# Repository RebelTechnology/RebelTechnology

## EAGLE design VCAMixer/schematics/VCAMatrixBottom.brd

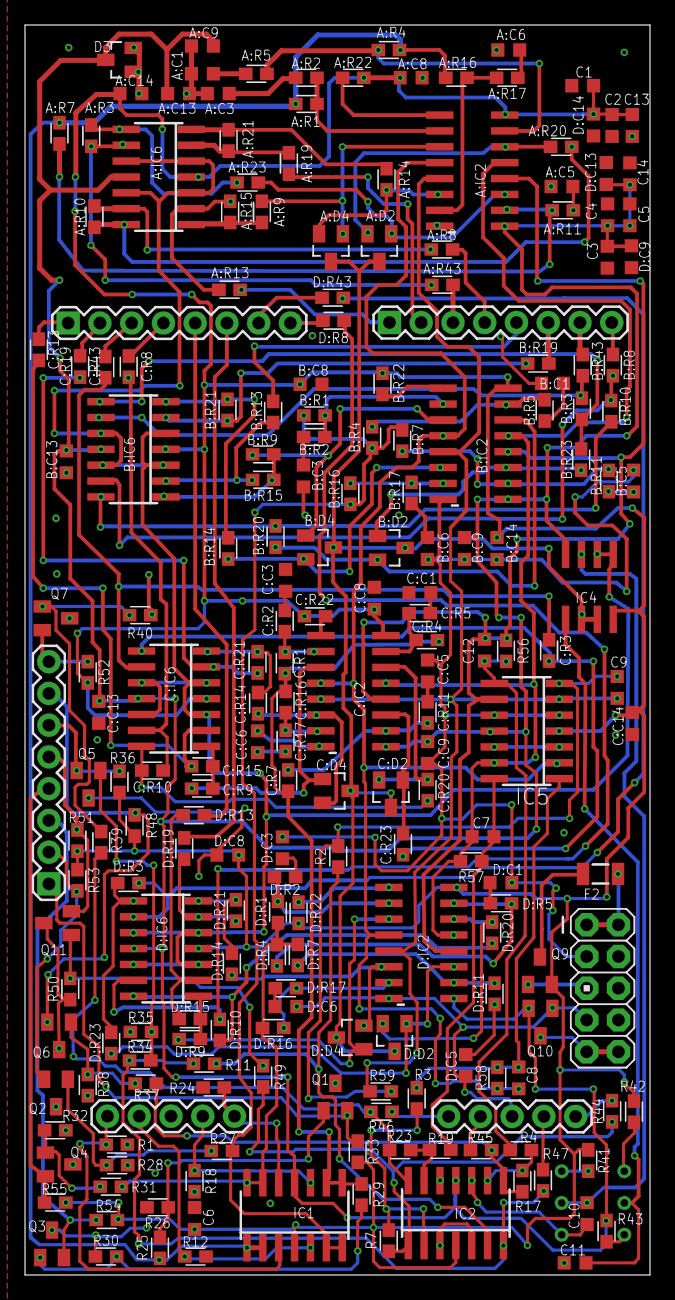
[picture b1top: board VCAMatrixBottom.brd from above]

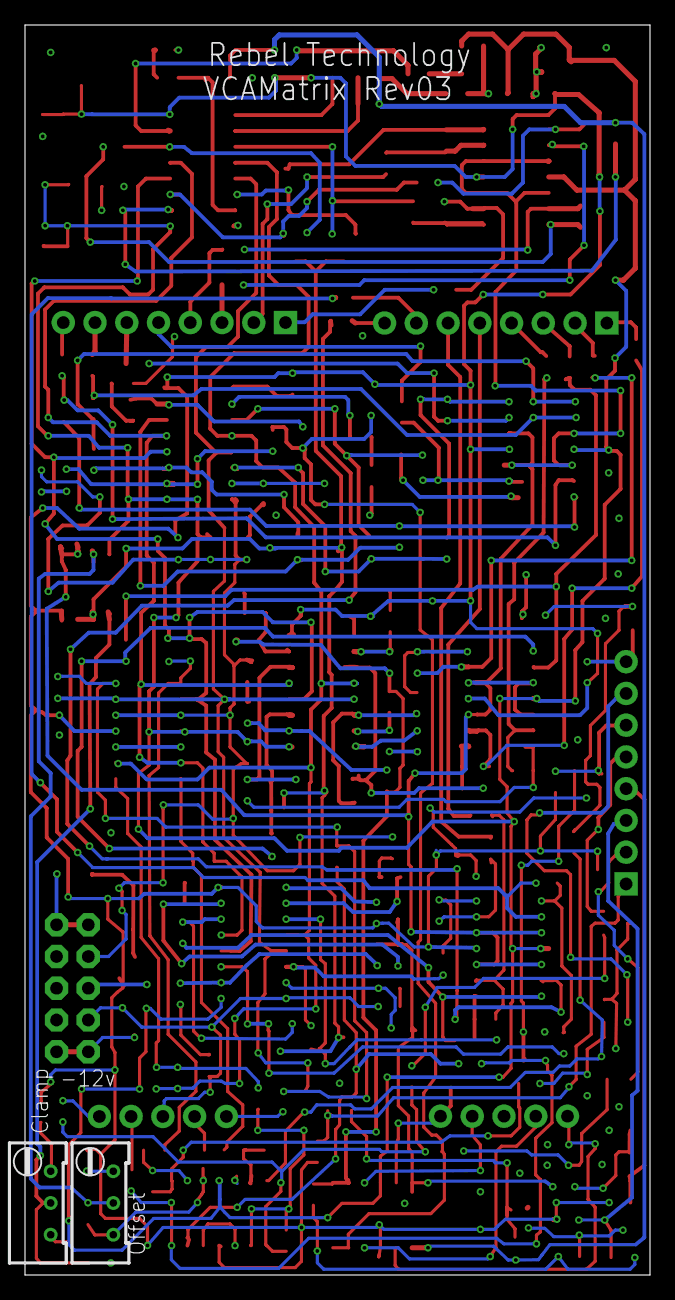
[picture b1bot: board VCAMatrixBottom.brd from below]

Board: 2 copper layers, 50.0 x 100.0 mm, 217 parts (2 on the bottom side), 157 nets.

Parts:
A:C1, A:C3, A:C5, A:C6: 560p; C0603K
A:C8, A:C9, A:C13, A:C14: 100n; C0603K
A:D2, A:D4: BAT54A; SOT23
A:IC2: SSM2164S; SOIC16N
A:IC6: QUAD_OPAMPD; SO14
A:R1, A:R4, A:R7, A:R16: 30k; 0603
A:R2, A:R5, A:R11, A:R17: 500; 0603
A:R3, A:R10, A:R15, A:R21: 68k; 0603
A:R8, A:R13, A:R19, A:R43: 100k; 0603
A:R9, A:R14, A:R20, A:R23: 560; 0603
A:R22: 5k6; 0603
B:C1, B:C3, B:C5, B:C6: 560p; C0603K
B:C8, B:C9, B:C13, B:C14: 100n; C0603K
B:D2, B:D4: BAT54A; SOT23
B:IC2: SSM2164S; SOIC16N
B:IC6: QUAD_OPAMPD; SO14
B:R1, B:R4, B:R7, B:R16: 30k; 0603
B:R2, B:R5, B:R11, B:R17: 500; 0603
B:R3, B:R10, B:R15, B:R21: 68k; 0603
B:R8, B:R13, B:R19, B:R43: 100k; 0603
B:R9, B:R14, B:R20, B:R23: 560; 0603
B:R22: 5k6; 0603
C1, C2, C3, C4, C5, C6, C13, C14: 100n; C0603K
C7, C8, C9, C12: 100p; C0603K
C10, C11: 4u7; C0603K
C:C1, C:C3, C:C5, C:C6: 560p; C0603K
C:C8, C:C9, C:C13, C:C14: 100n; C0603K
C:D2, C:D4: BAT54A; SOT23
C:IC2: SSM2164S; SOIC16N
C:IC6: QUAD_OPAMPD; SO14
C:R1, C:R4, C:R7, C:R16: 30k; 0603
C:R2, C:R5, C:R11, C:R17: 500; 0603
C:R3, C:R10, C:R15, C:R21: 68k; 0603
C:R8, C:R13, C:R19, C:R43: 100k; 0603
C:R9, C:R14, C:R20, C:R23: 560; 0603
C:R22: 5k6; 0603
CLAMP: RTRIM64W
D3: BAT54A; SOT23
D:C1, D:C3, D:C5, D:C6: 560p; C0603K
D:C8, D:C9, D:C13, D:C14: 100n; C0603K
D:D2, D:D4: BAT54A; SOT23
D:IC2: SSM2164S; SOIC16N
D:IC6: QUAD_OPAMPD; SO14
D:R1, D:R4, D:R7, D:R16: 30k; 0603
D:R2, D:R5, D:R11, D:R17: 500; 0603
D:R3, D:R10, D:R15, D:R21: 68k; 0603
D:R8, D:R13, D:R19, D:R43: 100k; 0603
D:R9, D:R14, D:R20, D:R23: 560; 0603
D:R22: 5k6; 0603
F2: PTCSMD; PTC-1206
IC1, IC2, IC5: QUAD_OPAMPD; SO14
IC4: TL072D; SO08
J3, J4: 1X05
JP1, JP3, JP5: 1X08
JP8: M05X2PTH; AVR_ICSP
OFFSET: RTRIM64W
Q1, Q2, Q3, Q4, Q5, Q6, Q7, Q11: BC856ALT1SMD; SOT23-BEC
Q9: BSS84; SOT23
Q10: BSS123; SOT23
R1, R2, R3, R4, R7, R11, R12, R17, R18, R19, R23, R24, R25, R27, R29, R31, R34, R37, R39, R49: 100k; 0603
R26, R28, R30, R32, R35, R38, R40, R50: 22k; 0603
R33, R36, R48, R51, R52, R53, R54, R55: 4k7; 0603
R41, R42, R43: 10k; 0603
R44, R45, R46, R47: 1k; 0603
R56, R57, R58, R59: 30k; 0603

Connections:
+12V: A:C8.1, A:C14.1, A:IC2.16, A:IC6.4, A:R22.2, B:C8.1, B:C14.1, B:IC2.16, B:IC6.4, B:R22.2, C1.1, C2.1, C6.1, C13.1, C:C8.1, C:C14.1, C:IC2.16, C:IC6.4, C:R22.2, D:C8.1, D:C14.1, D:IC2.16, D:IC6.4, D:R22.2, IC1.4, IC2.4, IC4.8, IC5.4, Q9.2, R33.2, R36.2, R41.2, R42.2, R48.2, R51.2, R52.2, R53.2, R54.2, R55.2
-12V: A:C9.2, A:C13.1, A:IC2.9, A:IC6.11, B:C9.2, B:C13.1, B:IC2.9, B:IC6.11, C3.1, C4.1, C5.1, C14.1, C:C9.2, C:C13.1, C:IC2.9, C:IC6.11, D3.3, D:C9.2, D:C13.1, D:IC2.9, D:IC6.11, IC1.11, IC2.11, IC4.4, IC5.11, Q10.2, R43.1
A:IC2_1: A:IC6.14, A:R10.1, A:R20.1
A:IC2_2: A:IC6.13, A:R8.1, A:R10.2
A:IC2_3: A:IC6.1, A:R9.1, A:R15.1
A:IC2_4: A:IC6.9, A:R3.2, A:R43.1
A:IC2_5: A:IC6.2, A:R13.1, A:R15.2
A:IC2_6: A:IC6.7, A:R14.1, A:R21.1
A:IC2_7: A:IC6.6, A:R19.1, A:R21.2
A:IC2_11: A:IC6.8, A:R3.1, A:R23.2
A:N$1: A:D4.1, A:IC2.3, A:R9.2
A:N$2: A:C1.1, A:R5.1
A:N$3: A:C3.1, A:R2.1
A:N$4: A:IC2.15, A:R4.2, A:R5.2
A:N$5: A:IC2.2, A:R1.2, A:R2.2
A:N$7: A:D4.2, A:IC2.6, A:R14.2
A:N$8: A:D2.1, A:IC2.11, A:R23.1
A:N$11: A:C6.1, A:R17.1
A:N$12: A:IC2.7, A:R16.2, A:R17.2
A:N$14: A:D2.2, A:IC2.14, A:R20.2
A:N$17: A:IC2.1, A:R22.1
A:N$19: A:C5.1, A:R11.1
A:N$23: A:IC2.10, A:R7.2, A:R11.2
B:IC2_1: B:IC6.14, B:R10.1, B:R20.1
B:IC2_2: B:IC6.13, B:R8.1, B:R10.2
B:IC2_3: B:IC6.1, B:R9.1, B:R15.1
B:IC2_4: B:IC6.9, B:R3.2, B:R43.1
B:IC2_5: B:IC6.2, B:R13.1, B:R15.2
B:IC2_6: B:IC6.7, B:R14.1, B:R21.1
B:IC2_7: B:IC6.6, B:R19.1, B:R21.2
B:IC2_11: B:IC6.8, B:R3.1, B:R23.2
B:N$1: B:D4.1, B:IC2.3, B:R9.2
B:N$2: B:C1.1, B:R5.1
B:N$3: B:C3.1, B:R2.1
B:N$4: B:IC2.15, B:R4.2, B:R5.2
B:N$5: B:IC2.2, B:R1.2, B:R2.2
B:N$7: B:D4.2, B:IC2.6, B:R14.2
B:N$8: B:D2.1, B:IC2.11, B:R23.1
B:N$11: B:C6.1, B:R17.1
B:N$12: B:IC2.7, B:R16.2, B:R17.2
B:N$14: B:D2.2, B:IC2.14, B:R20.2
B:N$17: B:IC2.1, B:R22.1
B:N$19: B:C5.1, B:R11.1
B:N$23: B:IC2.10, B:R7.2, B:R11.2
C:IC2_1: C:IC6.14, C:R10.1, C:R20.1
C:IC2_2: C:IC6.13, C:R8.1, C:R10.2
C:IC2_3: C:IC6.1, C:R9.1, C:R15.1
C:IC2_4: C:IC6.9, C:R3.2, C:R43.1
C:IC2_5: C:IC6.2, C:R13.1, C:R15.2
C:IC2_6: C:IC6.7, C:R14.1, C:R21.1
C:IC2_7: C:IC6.6, C:R19.1, C:R21.2
C:IC2_11: C:IC6.8, C:R3.1, C:R23.2
C:N$1: C:D4.1, C:IC2.3, C:R9.2
C:N$2: C:C1.1, C:R5.1
C:N$3: C:C3.1, C:R2.1
C:N$4: C:IC2.15, C:R4.2, C:R5.2
C:N$5: C:IC2.2, C:R1.2, C:R2.2
C:N$7: C:D4.2, C:IC2.6, C:R14.2
C:N$8: C:D2.1, C:IC2.11, C:R23.1
C:N$11: C:C6.1, C:R17.1
C:N$12: C:IC2.7, C:R16.2, C:R17.2
C:N$14: C:D2.2, C:IC2.14, C:R20.2
C:N$17: C:IC2.1, C:R22.1
C:N$19: C:C5.1, C:R11.1
C:N$23: C:IC2.10, C:R7.2, C:R11.2
CLAMP_REF: A:D2.3, A:D4.3, B:D2.3, B:D4.3, C:D2.3, C:D4.3, D:D2.3, D:D4.3, IC4.6, IC4.7
CV_AA: A:R13.2, JP1.1
CV_AB: A:R19.2, JP1.2
CV_AC: A:R43.2, JP1.3
CV_AD: A:R8.2, JP1.4
CV_BA: B:R13.2, JP1.5
CV_BB: B:R19.2, JP1.6
CV_BC: B:R43.2, JP1.7
CV_BD: B:R8.2, JP1.8
CV_CA: C:R13.2, JP3.1
CV_CB: C:R19.2, JP3.2
CV_CC: C:R43.2, JP3.3
CV_CD: C:R8.2, JP3.4
CV_DA: D:R13.2, JP3.5
CV_DB: D:R19.2, JP3.6
CV_DC: D:R43.2, JP3.7
CV_DD: D:R8.2, JP3.8
D:IC2_1: D:IC6.14, D:R10.1, D:R20.1
D:IC2_2: D:IC6.13, D:R8.1, D:R10.2
D:IC2_3: D:IC6.1, D:R9.1, D:R15.1
D:IC2_4: D:IC6.9, D:R3.2, D:R43.1
D:IC2_5: D:IC6.2, D:R13.1, D:R15.2
D:IC2_6: D:IC6.7, D:R14.1, D:R21.1
D:IC2_7: D:IC6.6, D:R19.1, D:R21.2
D:IC2_11: D:IC6.8, D:R3.1, D:R23.2
D:N$1: D:D4.1, D:IC2.3, D:R9.2
D:N$2: D:C1.1, D:R5.1
D:N$3: D:C3.1, D:R2.1
D:N$4: D:IC2.15, D:R4.2, D:R5.2
D:N$5: D:IC2.2, D:R1.2, D:R2.2
D:N$7: D:D4.2, D:IC2.6, D:R14.2
D:N$8: D:D2.1, D:IC2.11, D:R23.1
D:N$11: D:C6.1, D:R17.1
D:N$12: D:IC2.7, D:R16.2, D:R17.2
D:N$14: D:D2.2, D:IC2.14, D:R20.2
D:N$17: D:IC2.1, D:R22.1
D:N$19: D:C5.1, D:R11.1
D:N$23: D:IC2.10, D:R7.2, D:R11.2
GND: A:C1.2, A:C3.2, A:C5.2, A:C6.2, A:C8.2, A:C9.1, A:C13.2, A:C14.2, A:IC2.8, B:C1.2, B:C3.2, B:C5.2, B:C6.2, B:C8.2, B:C9.1, B:C13.2, B:C14.2, B:IC2.8, C1.2, C2.2, C3.2, C4.2, C5.2, C6.2, C10.2, C11.2, C13.2, C14.2, C:C1.2, C:C3.2, C:C5.2, C:C6.2, C:C8.2, C:C9.1, C:C13.2, C:C14.2, C:IC2.8, D3.1, D3.2, D:C1.2, D:C3.2, D:C5.2, D:C6.2, D:C8.2, D:C9.1, D:C13.2, D:C14.2, D:IC2.8, IC2.3, IC2.5, IC2.10, IC2.12, IC5.3, IC5.5, IC5.10, IC5.12, J3.3, J4.3, JP8.3, JP8.4, JP8.5, JP8.6, JP8.7, JP8.8, OFFSET.1, Q1.C, Q2.C, Q3.C, Q4.C, Q5.C, Q6.C, Q7.C, Q9.1, Q10.1, Q11.C, R1.1, R12.1, R18.1, R24.1, R26.1, R28.1, R30.1, R32.1, R35.1, R38.1, R40.1, R50.1
IN_A: IC1.3, J3.5, R1.2
IN_B: IC1.5, J3.4, R12.2
IN_C: IC1.10, J3.2, R18.2
IN_D: IC1.12, J3.1, R24.2
ITOV_A: C8.1, IC5.1, R3.1, R58.2
ITOV_B: C9.1, IC5.7, R2.1, R59.2
ITOV_C: C12.1, IC5.8, R4.1, R56.2
ITOV_D: C7.1, IC5.14, R19.1, R57.2
LED_1: JP5.1, Q1.E, R33.1
LED_2: JP5.2, Q2.E, R53.1
LED_3: JP5.3, Q3.E, R54.1
LED_4: JP5.4, Q4.E, R55.1
LED_5: JP5.5, Q11.E, R51.1
LED_6: JP5.6, Q5.E, R36.1
LED_7: JP5.7, Q6.E, R48.1
LED_8: JP5.8, Q7.E, R52.1
unnamed: B:R1.1, B:R4.1, B:R7.1, B:R16.1, IC1.6, IC1.7, R27.1
unnamed: Q1.B, R25.2, R26.2
unnamed: JP8.9, JP8.10, Q10.3
unnamed: Q2.B, R27.2, R28.2
unnamed: IC2.2, R3.2, R7.1
unnamed: A:IC2.4, B:IC2.4, C8.2, C:IC2.4, D:IC2.4, IC5.2, R58.1
unnamed: A:IC2.12, B:IC2.12, C12.2, C:IC2.12, D:IC2.12, IC5.9, R56.1
unnamed: A:IC2.5, B:IC2.5, C9.2, C:IC2.5, D:IC2.5, IC5.6, R59.1
unnamed: IC2.9, R4.2, R17.1
unnamed: Q11.B, R49.2, R50.2
unnamed: OFFSET.3, R41.1
unnamed: Q5.B, R34.2, R35.2
unnamed: Q6.B, R37.2, R38.2
unnamed: Q7.B, R39.2, R40.2
unnamed: F2.2, Q9.3
unnamed: A:IC2.13, B:IC2.13, C7.2, C:IC2.13, D:IC2.13, IC5.13, R57.1
unnamed: Q3.B, R29.2, R30.2
unnamed: D:R1.1, D:R4.1, D:R7.1, D:R16.1, IC1.13, IC1.14, R31.1
unnamed: C:R1.1, C:R4.1, C:R7.1, C:R16.1, IC1.8, IC1.9, R29.1
unnamed: Q4.B, R31.2, R32.2
unnamed: C10.1, IC4.3, OFFSET.2
unnamed: CLAMP.3, R42.1
unnamed: IC2.13, R19.2, R23.1
unnamed: IC2.6, R2.2, R11.1
unnamed: CLAMP.1, R43.2
unnamed: C11.1, CLAMP.2, IC4.5
unnamed: F2.1, JP8.1, JP8.2
unnamed: A:R1.1, A:R4.1, A:R7.1, A:R16.1, IC1.1, IC1.2, R25.1
OFFSET_REF: A:IC6.3, A:IC6.5, A:IC6.10, A:IC6.12, B:IC6.3, B:IC6.5, B:IC6.10, B:IC6.12, C:IC6.3, C:IC6.5, C:IC6.10, C:IC6.12, D:IC6.3, D:IC6.5, D:IC6.10, D:IC6.12, IC4.1, IC4.2
OUTPUT_A: J4.5, R44.1
OUTPUT_B: J4.4, R47.1
OUTPUT_C: J4.2, R45.1
OUTPUT_D: J4.1, R46.1
OUT_A: IC2.1, R7.2, R44.2, R49.1
OUT_B: IC2.7, R11.2, R34.1, R47.2
OUT_C: IC2.8, R17.2, R37.1, R45.2
OUT_D: IC2.14, R23.2, R39.1, R46.2

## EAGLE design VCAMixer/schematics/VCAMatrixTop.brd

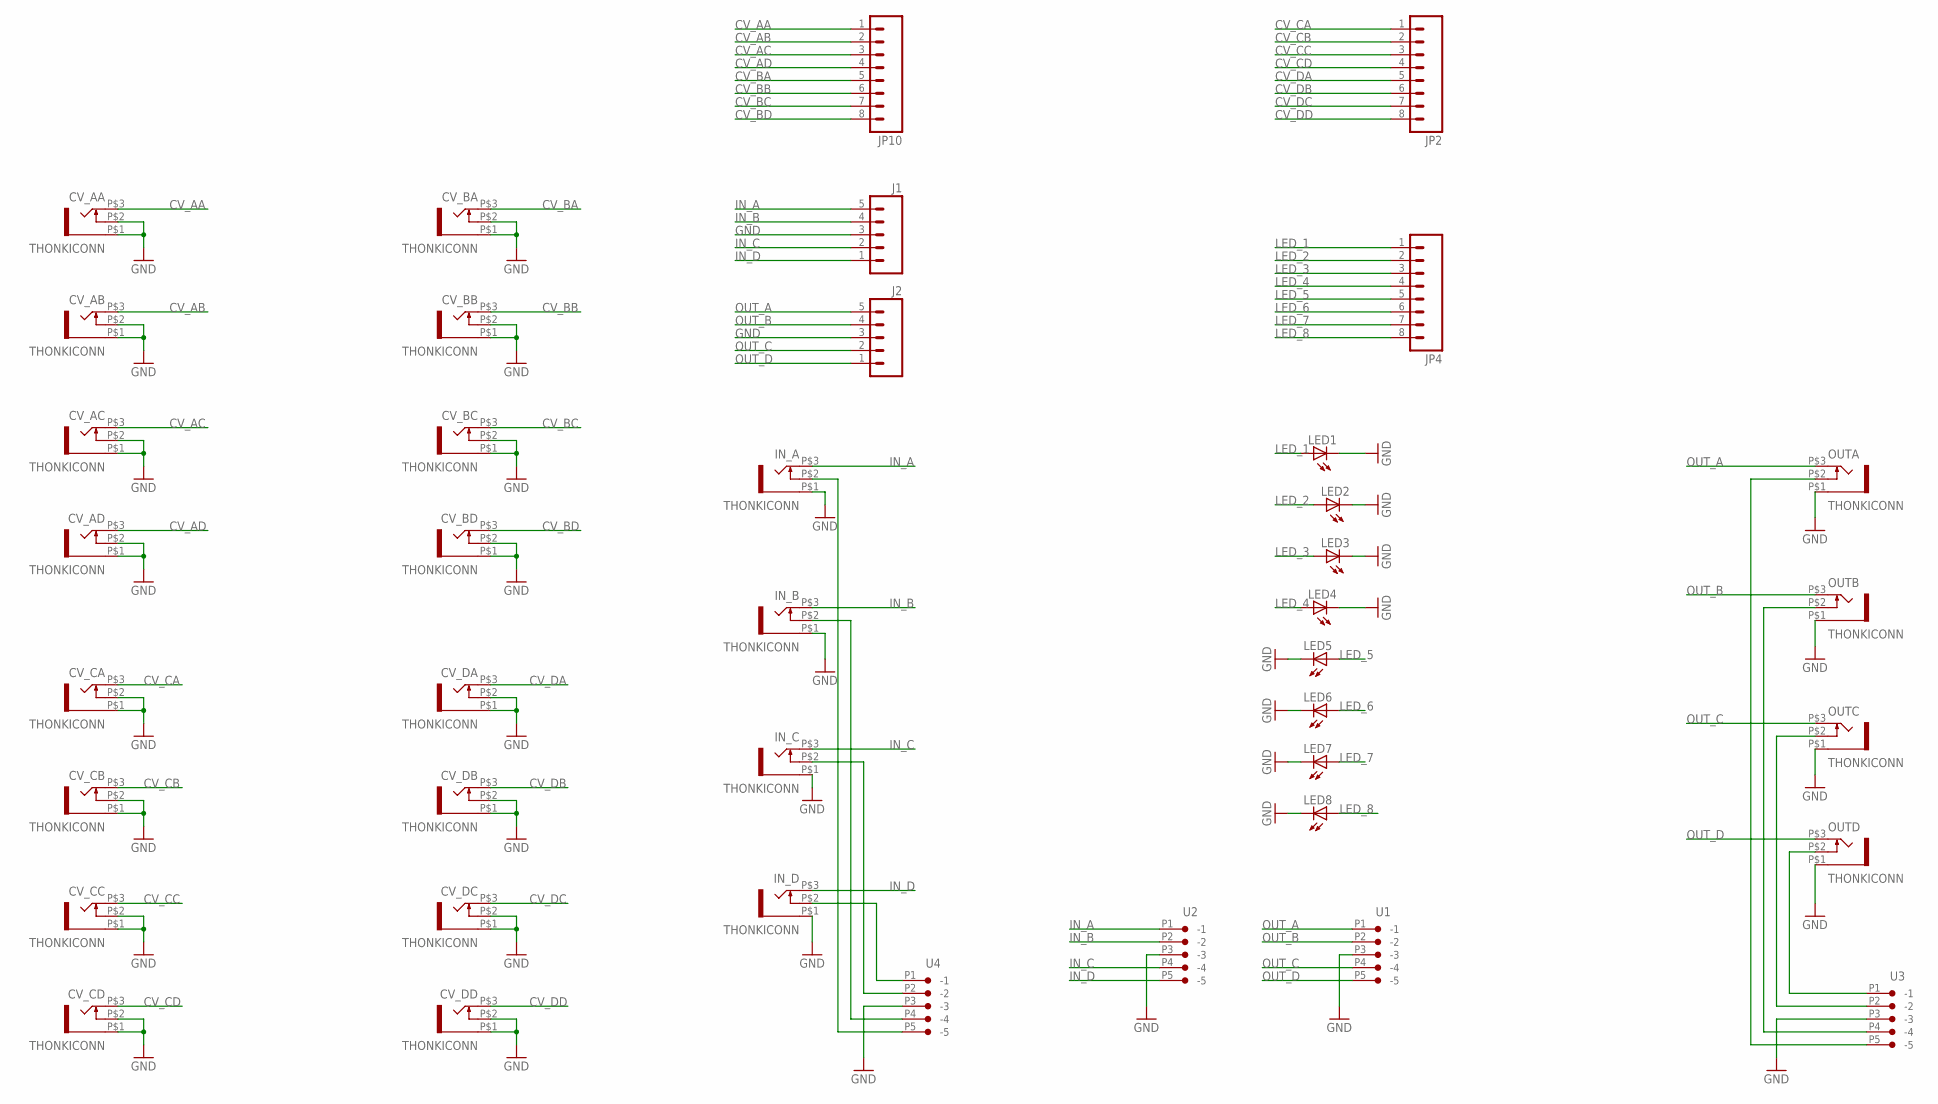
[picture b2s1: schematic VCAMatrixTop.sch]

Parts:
CV_AA: THONKICONN
CV_AB: THONKICONN
CV_AC: THONKICONN
CV_AD: THONKICONN
CV_BA: THONKICONN
CV_BB: THONKICONN
CV_BC: THONKICONN
CV_BD: THONKICONN
CV_CA: THONKICONN
CV_CB: THONKICONN
CV_CC: THONKICONN
CV_CD: THONKICONN
CV_DA: THONKICONN
CV_DB: THONKICONN
CV_DC: THONKICONN
CV_DD: THONKICONN
IN_A: THONKICONN
IN_B: THONKICONN
IN_C: THONKICONN
IN_D: THONKICONN
J1, J2: M05PTH; 1X05
JP2, JP4, JP10: M081X08; 1X08
LED1, LED2, LED3, LED4, LED5, LED6, LED7, LED8: LED3MM
OUTA: THONKICONN
OUTB: THONKICONN
OUTC: THONKICONN
OUTD: THONKICONN
U1, U2, U3, U4: CON-JST_PH_5W

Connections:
CV_AA: CV_AA.P$3 (3), JP10.1
CV_AB: CV_AB.P$3 (3), JP10.2
CV_AC: CV_AC.P$3 (3), JP10.3
CV_AD: CV_AD.P$3 (3), JP10.4
CV_BA: CV_BA.P$3 (3), JP10.5
CV_BB: CV_BB.P$3 (3), JP10.6
CV_BC: CV_BC.P$3 (3), JP10.7
CV_BD: CV_BD.P$3 (3), JP10.8
CV_CA: CV_CA.P$3 (3), JP2.1
CV_CB: CV_CB.P$3 (3), JP2.2
CV_CC: CV_CC.P$3 (3), JP2.3
CV_CD: CV_CD.P$3 (3), JP2.4
CV_DA: CV_DA.P$3 (3), JP2.5
CV_DB: CV_DB.P$3 (3), JP2.6
CV_DC: CV_DC.P$3 (3), JP2.7
CV_DD: CV_DD.P$3 (3), JP2.8
GND: CV_AA.P$1 (5), CV_AA.P$2 (4), CV_AB.P$1 (5), CV_AB.P$2 (4), CV_AC.P$1 (5), CV_AC.P$2 (4), CV_AD.P$1 (5), CV_AD.P$2 (4), CV_BA.P$1 (5), CV_BA.P$2 (4), CV_BB.P$1 (5), CV_BB.P$2 (4), CV_BC.P$1 (5), CV_BC.P$2 (4), CV_BD.P$1 (5), CV_BD.P$2 (4), CV_CA.P$1 (5), CV_CA.P$2 (4), CV_CB.P$1 (5), CV_CB.P$2 (4), CV_CC.P$1 (5), CV_CC.P$2 (4), CV_CD.P$1 (5), CV_CD.P$2 (4), CV_DA.P$1 (5), CV_DA.P$2 (4), CV_DB.P$1 (5), CV_DB.P$2 (4), CV_DC.P$1 (5), CV_DC.P$2 (4), CV_DD.P$1 (5), CV_DD.P$2 (4), IN_A.P$1 (5), IN_B.P$1 (5), IN_C.P$1 (5), IN_D.P$1 (5), J1.3, J2.3, LED1.K (C), LED2.K (C), LED3.K (C), LED4.K (C), LED5.K (C), LED6.K (C), LED7.K (C), LED8.K (C), OUTA.P$1 (5), OUTB.P$1 (5), OUTC.P$1 (5), OUTD.P$1 (5), U1.P3 (-3), U2.P3 (-3), U3.P3 (-3), U4.P3 (-3)
IN_A: IN_A.P$3 (3), J1.5, U2.P1 (-1)
IN_B: IN_B.P$3 (3), J1.4, U2.P2 (-2)
IN_C: IN_C.P$3 (3), J1.2, U2.P4 (-4)
IN_D: IN_D.P$3 (3), J1.1, U2.P5 (-5)
LED_1: JP4.1, LED1.A
LED_2: JP4.2, LED2.A
LED_3: JP4.3, LED3.A
LED_4: JP4.4, LED4.A
LED_5: JP4.5, LED5.A
LED_6: JP4.6, LED6.A
LED_7: JP4.7, LED7.A
LED_8: JP4.8, LED8.A
unnamed: OUTA.P$2 (4), U3.P5 (-5)
unnamed: IN_B.P$2 (4), U4.P4 (-4)
unnamed: IN_C.P$2 (4), U4.P2 (-2)
unnamed: IN_D.P$2 (4), U4.P1 (-1)
unnamed: OUTB.P$2 (4), U3.P4 (-4)
unnamed: OUTC.P$2 (4), U3.P2 (-2)
unnamed: OUTD.P$2 (4), U3.P1 (-1)
unnamed: IN_A.P$2 (4), U4.P5 (-5)
OUT_A: J2.5, OUTA.P$3 (3), U1.P1 (-1)
OUT_B: J2.4, OUTB.P$3 (3), U1.P2 (-2)
OUT_C: J2.2, OUTC.P$3 (3), U1.P4 (-4)
OUT_D: J2.1, OUTD.P$3 (3), U1.P5 (-5)

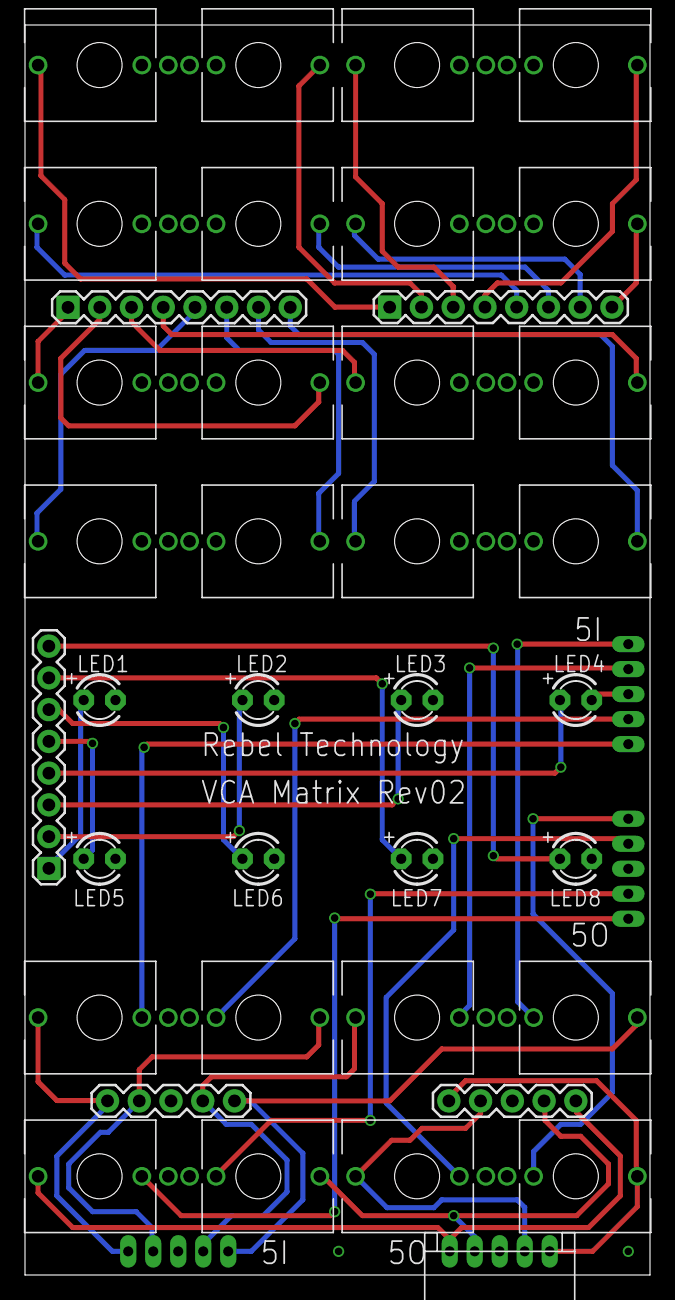
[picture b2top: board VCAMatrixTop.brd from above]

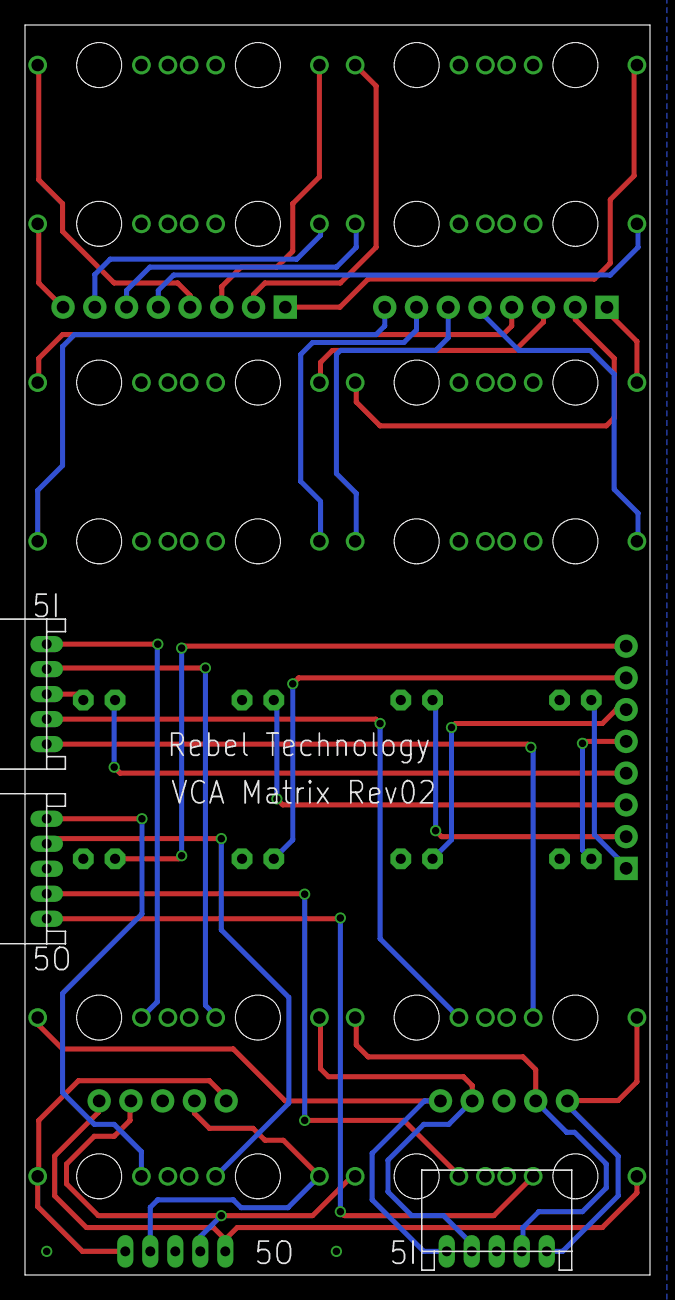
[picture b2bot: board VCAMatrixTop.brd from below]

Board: 2 copper layers, 50.0 x 100.0 mm, 41 parts (3 on the bottom side), 41 nets.

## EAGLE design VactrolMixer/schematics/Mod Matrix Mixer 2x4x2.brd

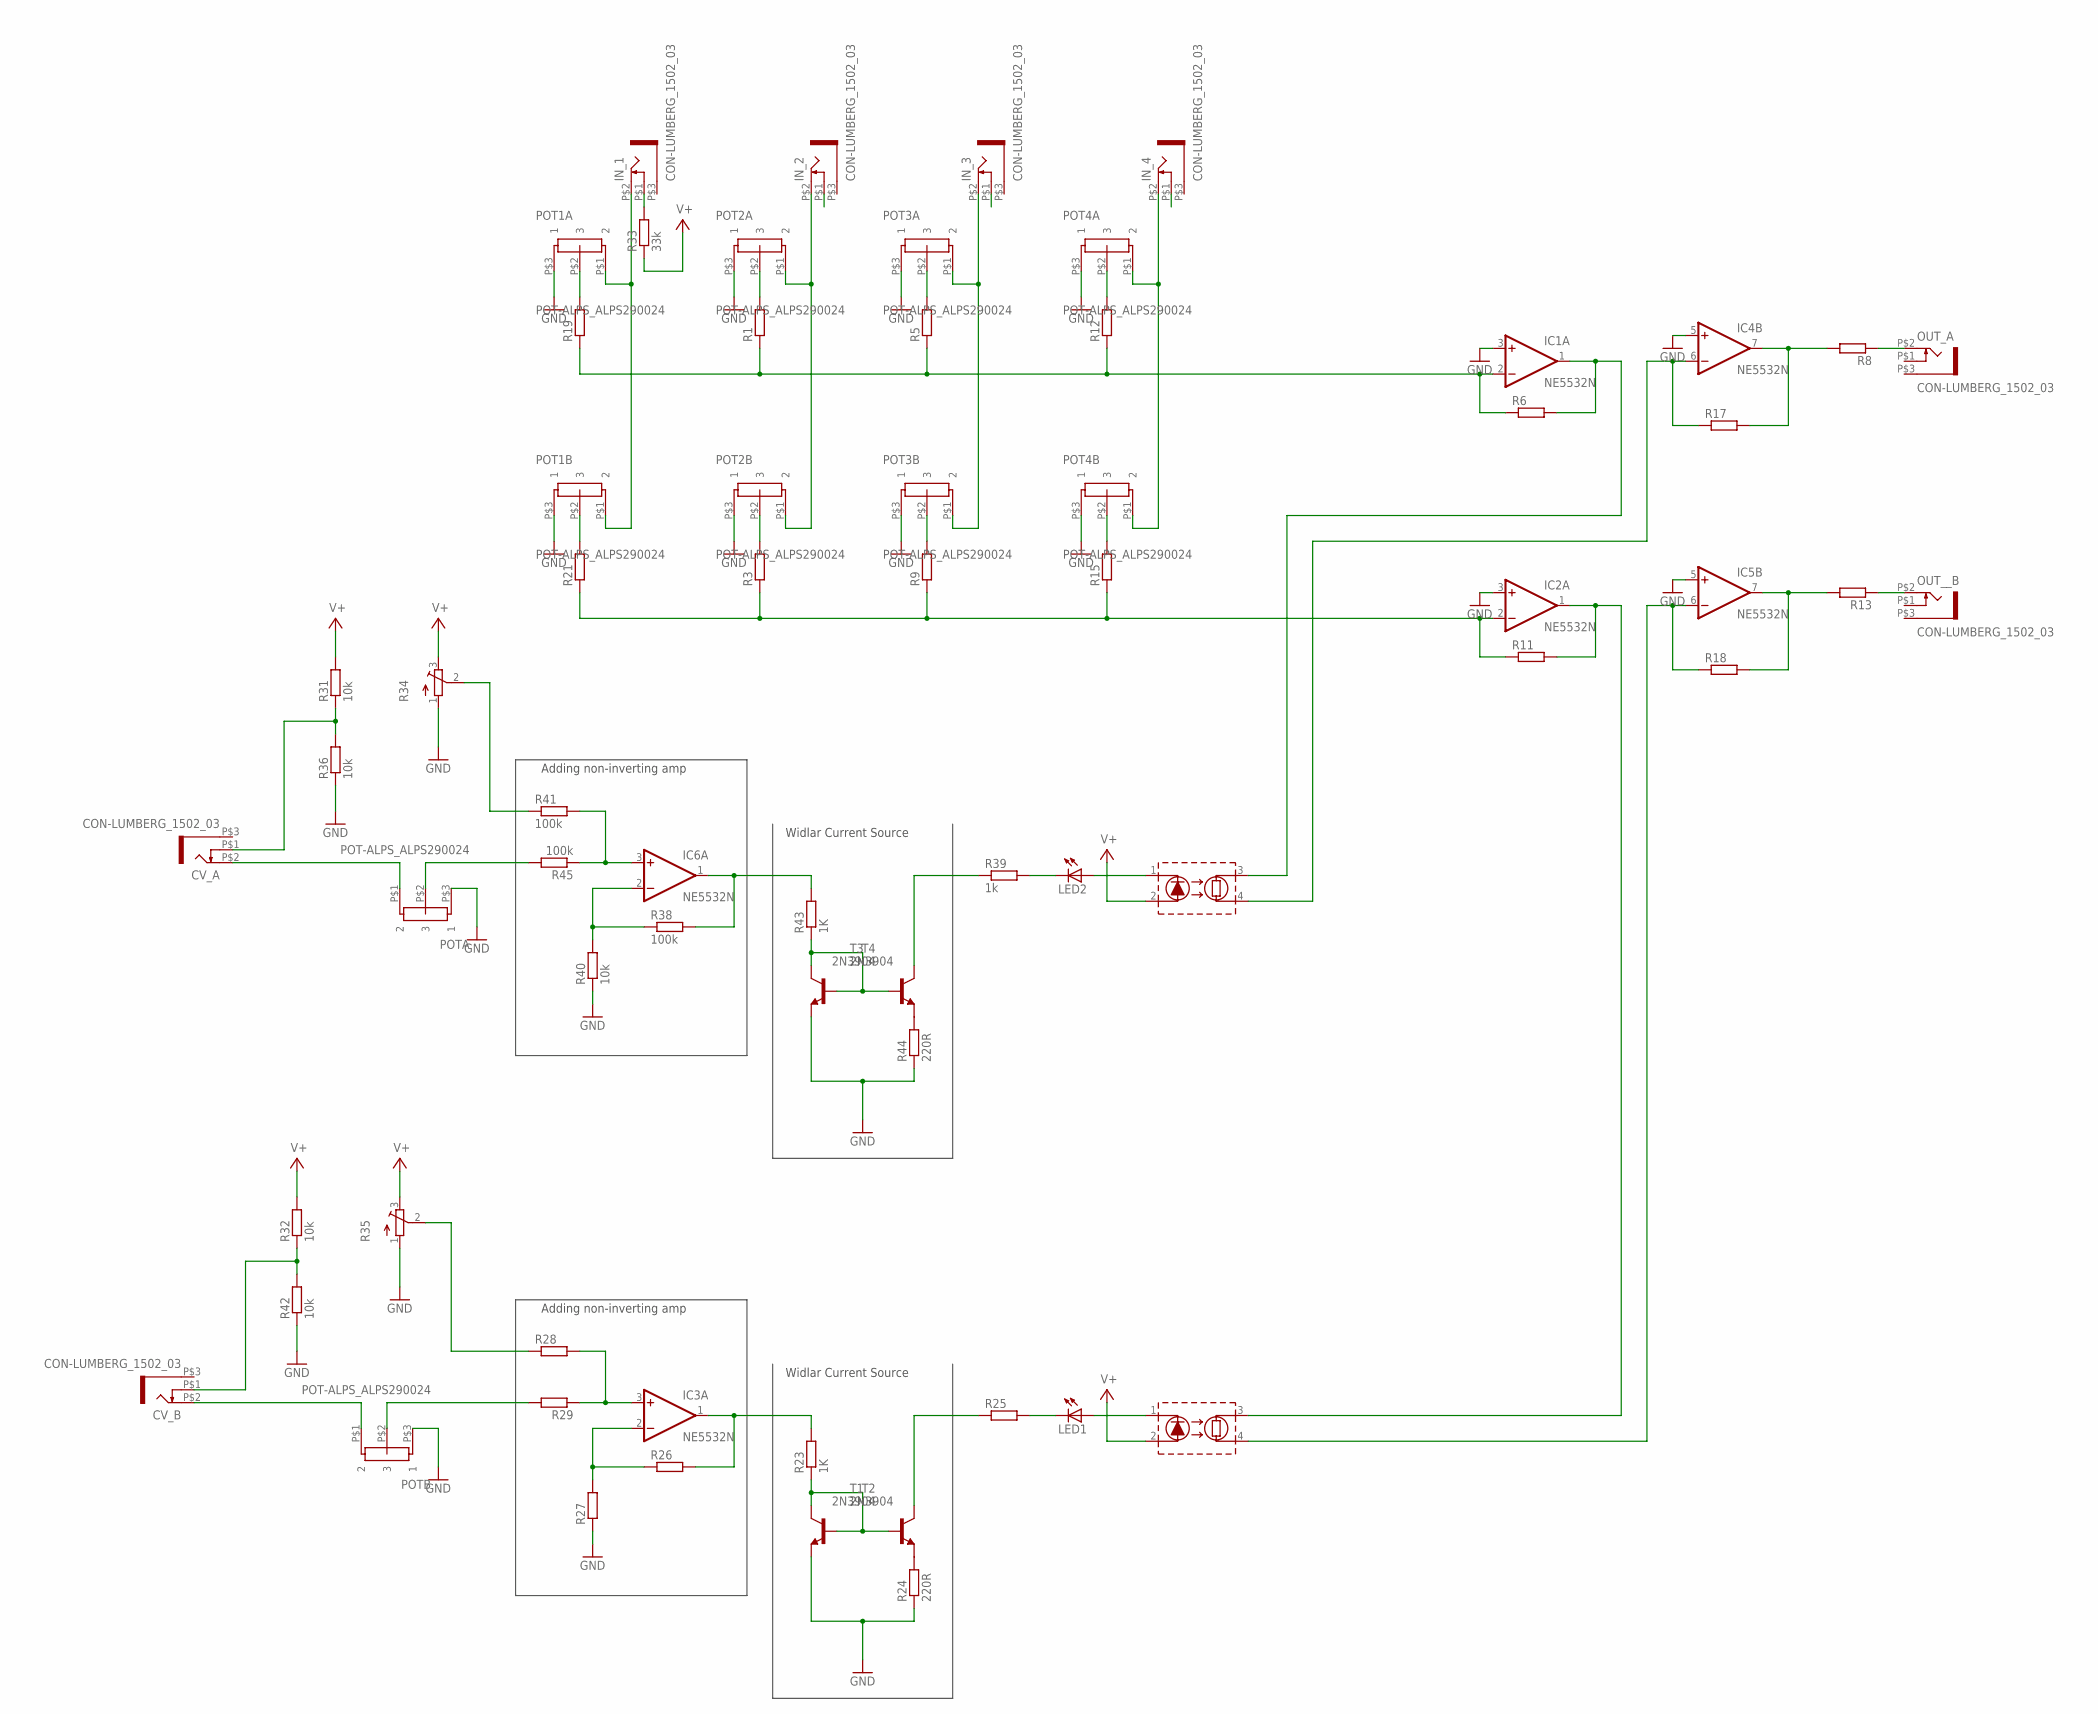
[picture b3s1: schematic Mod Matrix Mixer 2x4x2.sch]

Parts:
CV_A: CON-LUMBERG_1502_03
CV_B: CON-LUMBERG_1502_03
IC1, IC2, IC3, IC4, IC5, IC6: NE5532N; DIL08
IN_1, IN_2, IN_3, IN_4: CON-LUMBERG_1502_03
LED1, LED2: LED5MM
OUT_A: CON-LUMBERG_1502_03
OUT__B: CON-LUMBERG_1502_03
POT1A, POT1B, POT2A, POT2B, POT3A, POT3B, POT4A, POT4B: POT-ALPS_ALPS290024; POT-ALPS_POT
POTA: POT-ALPS_ALPS290024; POT-ALPS_POT
POTB: POT-ALPS_ALPS290024; POT-ALPS_POT
R1, R3, R5, R6, R8, R9, R11, R12, R13, R15, R17, R18, R19, R21, R25, R26, R27, R28, R29: R-EU_0411/15; 0411/15
R23, R43: 1K; 0411/15
R24, R44: 220R; 0411/15
R31, R32, R36, R40, R42: 10k; 0411/15
R33: 33k; 0411/15
R34, R35: TRIM_EU-3223W; 3223W
R38, R41, R45: 100k; 0411/15
R39: 1k; 0411/15
T1, T2, T3, T4: 2N3904; TO92
U$1, U$2: VTL5C3

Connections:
GND: IC1.3 (+IN), IC2.3 (+IN), IC4.5 (+IN), IC5.5 (+IN), POT1A.P$3 (1), POT1B.P$3 (1), POT2A.P$3 (1), POT2B.P$3 (1), POT3A.P$3 (1), POT3B.P$3 (1), POT4A.P$3 (1), POT4B.P$3 (1), POTA.P$3 (1), POTB.P$3 (1), R24.1, R27.1, R34.1 (A), R35.1 (A), R36.1, R40.1, R42.1, R44.1, T2.3 (E), T4.3 (E)
IN_C: IN_3.P$1 (4)
unnamed: IC4.7 (OUT), R8.2, R17.2
unnamed: IN_2.P$2 (3), POT2A.P$1 (2), POT2B.P$1 (2)
unnamed: IC2.1 (OUT), R11.2, U$1.3 (LDRA)
unnamed: IC1.1 (OUT), R6.2, U$2.3 (LDRA)
unnamed: OUT_A.P$2 (3), R8.1
unnamed: OUT__B.P$2 (3), R13.1
unnamed: POT1A.P$2 (3), R19.2
unnamed: POT1B.P$2 (3), R21.2
unnamed: IC4.6 (-IN), R17.1, U$2.4 (LDRB)
unnamed: POT2A.P$2 (3), R1.2
unnamed: POT2B.P$2 (3), R3.2
unnamed: IC5.7 (OUT), R13.2, R18.2
unnamed: LED1.A, U$1.1 (LED-)
unnamed: LED1.K (C), R25.2
unnamed: IC3.1 (OUT), R23.2, R26.2
unnamed: POTA.P$2 (3), R45.2
unnamed: IN_3.P$2 (3), POT3A.P$1 (2), POT3B.P$1 (2)
unnamed: POT3A.P$2 (3), R5.2
unnamed: POT3B.P$2 (3), R9.2
unnamed: CV_A.P$2 (3), POTA.P$1 (2)
unnamed: CV_A.P$1 (4), R31.1, R36.2
unnamed: IN_4.P$2 (3), POT4A.P$1 (2), POT4B.P$1 (2)
unnamed: IN_1.P$2 (3), POT1A.P$1 (2), POT1B.P$1 (2)
unnamed: R24.2, T1.3 (E)
unnamed: R23.1, T1.2 (B), T2.1 (C), T2.2 (B)
unnamed: R25.1, T1.1 (C)
unnamed: IC3.2 (-IN), R26.1, R27.2
unnamed: R28.1, R35.2 (S)
unnamed: IC3.3 (+IN), R28.2, R29.1
unnamed: R44.2, T3.3 (E)
unnamed: IC5.6 (-IN), R18.1, U$1.4 (LDRB)
unnamed: POTB.P$2 (3), R29.2
unnamed: CV_B.P$2 (3), POTB.P$1 (2)
unnamed: LED2.A, U$2.1 (LED-)
unnamed: LED2.K (C), R39.2
unnamed: R39.1, T3.1 (C)
unnamed: IC6.1 (OUT), R38.2, R43.2
unnamed: IN_1.P$1 (4), R33.2
unnamed: R43.1, T3.2 (B), T4.1 (C), T4.2 (B)
unnamed: POT4A.P$2 (3), R12.2
unnamed: POT4B.P$2 (3), R15.2
unnamed: CV_B.P$1 (4), R32.1, R42.2
unnamed: IC6.2 (-IN), R38.1, R40.2
unnamed: IC6.3 (+IN), R41.2, R45.1
unnamed: R34.2 (S), R41.1
unnamed: IC1.2 (-IN), R1.1, R5.1, R6.1, R12.1, R19.1
unnamed: IC2.2 (-IN), R3.1, R9.1, R11.1, R15.1, R21.1
V+: IC1.8 (V+), IC2.8 (V+), IC3.8 (V+), IC4.8 (V+), IC5.8 (V+), IC6.8 (V+), R31.2, R32.2, R33.1, R34.3 (E), R35.3 (E), U$1.2 (LED+), U$2.2 (LED+)
V-: IC1.4 (V-), IC2.4 (V-), IC3.4 (V-), IC4.4 (V-), IC5.4 (V-), IC6.4 (V-)

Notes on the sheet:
Widlar Current Source
Adding non-inverting amp

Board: 2 copper layers, 67 parts (0 on the bottom side), 50 nets, no tracks yet.

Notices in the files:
parts and their libraries:
SparkFun: Licensing: CC v3.0 Share-Alike You are welcome to use this library for commercial purposes.
SparkFun-Connectors: Licensing: Creative Commons ShareAlike 4.0 International - https://creativecommons.org/licenses/by-sa/4.0
